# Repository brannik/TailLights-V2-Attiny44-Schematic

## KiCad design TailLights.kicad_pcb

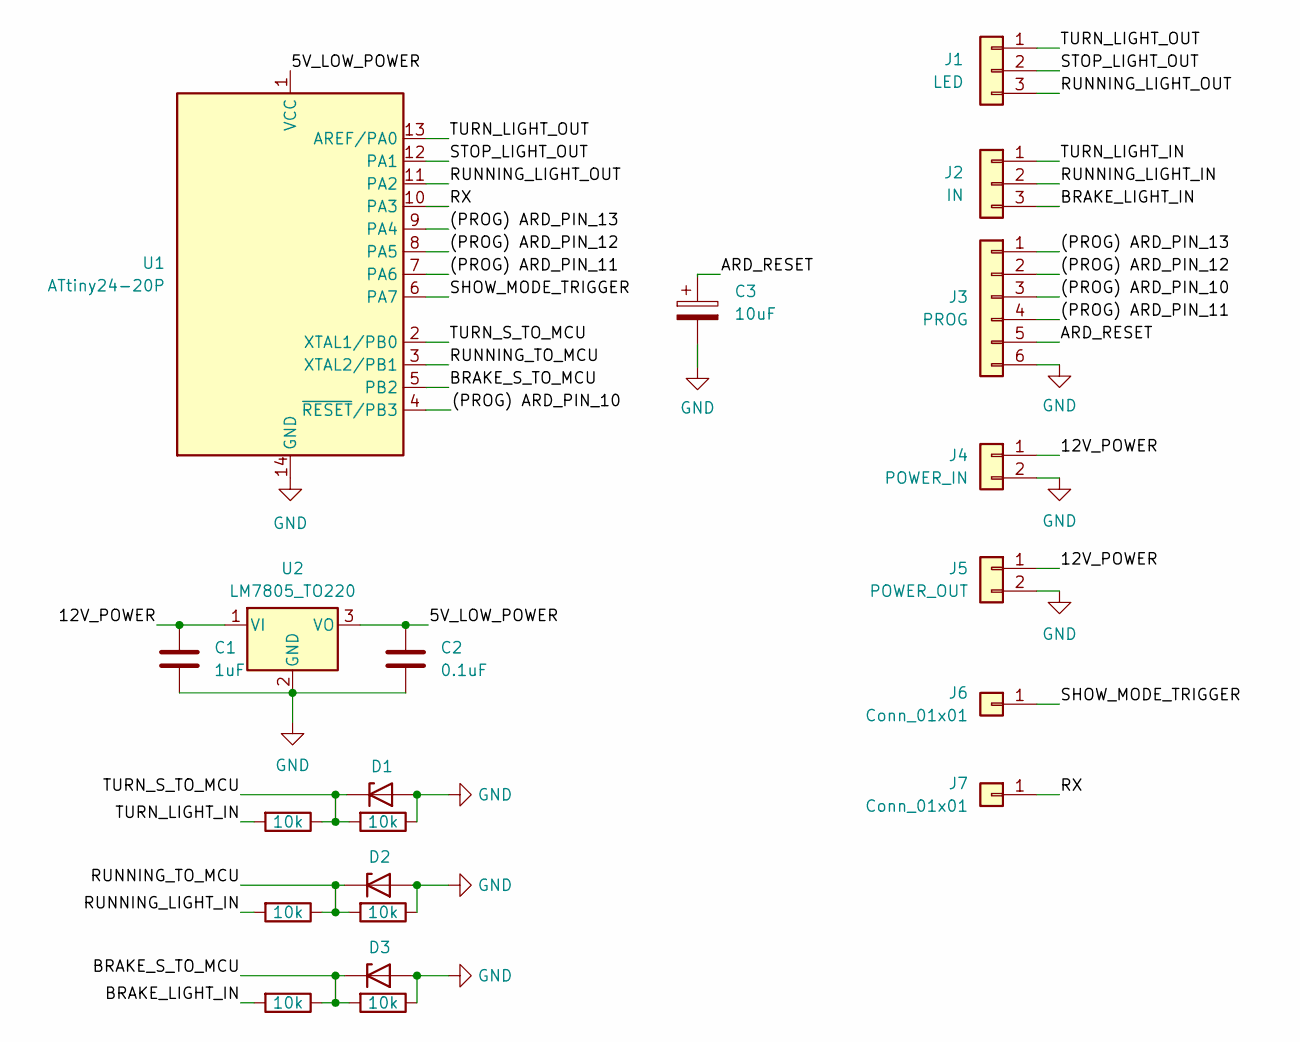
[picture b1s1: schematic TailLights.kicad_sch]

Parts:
C1: 1uF; C_Disc_D10.0mm_W2.5mm_P5.00mm
C2: 0.1uF; C_Disc_D10.0mm_W2.5mm_P5.00mm
C3: 10uF; CP_Radial_D10.0mm_P5.00mm
D1, D2, D3: 1N47xxA; D_DO-41_SOD81_P3.81mm_Vertical_AnodeUp
J1: LED; PinSocket_1x03_P2.54mm_Vertical
J2: IN; PinSocket_1x03_P2.54mm_Vertical
J3: PROG; PinSocket_1x06_P2.54mm_Vertical
J4: POWER_IN; PinSocket_1x02_P2.54mm_Vertical
J5: POWER_OUT; PinSocket_1x02_P2.54mm_Vertical
J6, J7: Conn_01x01; PinSocket_1x01_P2.54mm_Vertical
R1, R2, R3, R4, R5, R6: 10k; R_Axial_DIN0207_L6.3mm_D2.5mm_P2.54mm_Vertical
U1: ATtiny24-20P; DIP-14_W7.62mm
U2: LM7805_TO220; TO-220-3_Vertical

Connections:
/5V_LOW_POWER: C2.1, U1.1 (VCC), U2.3 (VO)
/12V_POWER: C1.1, J4.1, J5.1, U2.1 (VI)
/(PROG) ARD_PIN_10: J3.3, U1.4 (~RESET/PB3)
/(PROG) ARD_PIN_11: J3.4, U1.7 (PA6)
/(PROG) ARD_PIN_12: J3.2, U1.8 (PA5)
/(PROG) ARD_PIN_13: J3.1, U1.9 (PA4)
/ARD_RESET: C3.1, J3.5
/BRAKE_LIGHT_IN: J2.3, R5.2
/BRAKE_S_TO_MCU: D3.1 (K), R5.1, R6.2, U1.5 (PB2)
/RUNNING_LIGHT_IN: J2.2, R3.2
/RUNNING_LIGHT_OUT: J1.3, U1.11 (PA2)
/RUNNING_TO_MCU: D2.1 (K), R3.1, R4.2, U1.3 (XTAL2/PB1)
/RX: J7.1, U1.10 (PA3)
/SHOW_MODE_TRIGGER: J6.1, U1.6 (PA7)
/STOP_LIGHT_OUT: J1.2, U1.12 (PA1)
/TURN_LIGHT_IN: J2.1, R1.2
/TURN_LIGHT_OUT: J1.1, U1.13 (AREF/PA0)
/TURN_S_TO_MCU: D1.1 (K), R1.1, R2.2, U1.2 (XTAL1/PB0)
GND: C1.2, C2.2, C3.2, D1.2 (A), D2.2 (A), D3.2 (A), J3.6, J4.2, J5.2, R2.1, R4.1, R6.1, U1.14 (GND), U2.2 (GND)

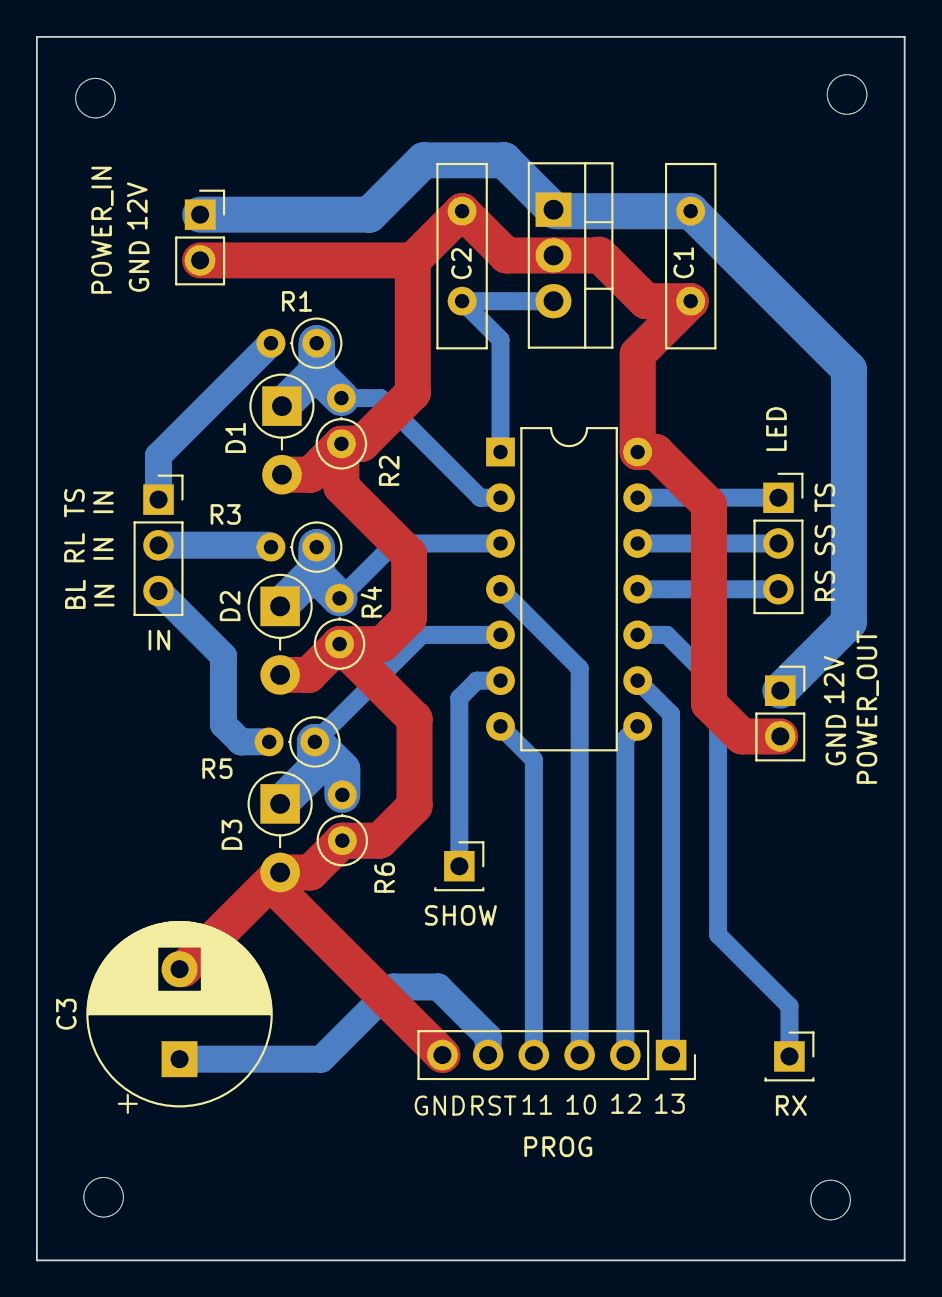
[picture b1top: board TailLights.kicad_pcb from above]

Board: 2 copper layers, 48.2 x 68.0 mm, 21 parts (0 on the bottom side), 19 nets.

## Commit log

2023-09-18 init
